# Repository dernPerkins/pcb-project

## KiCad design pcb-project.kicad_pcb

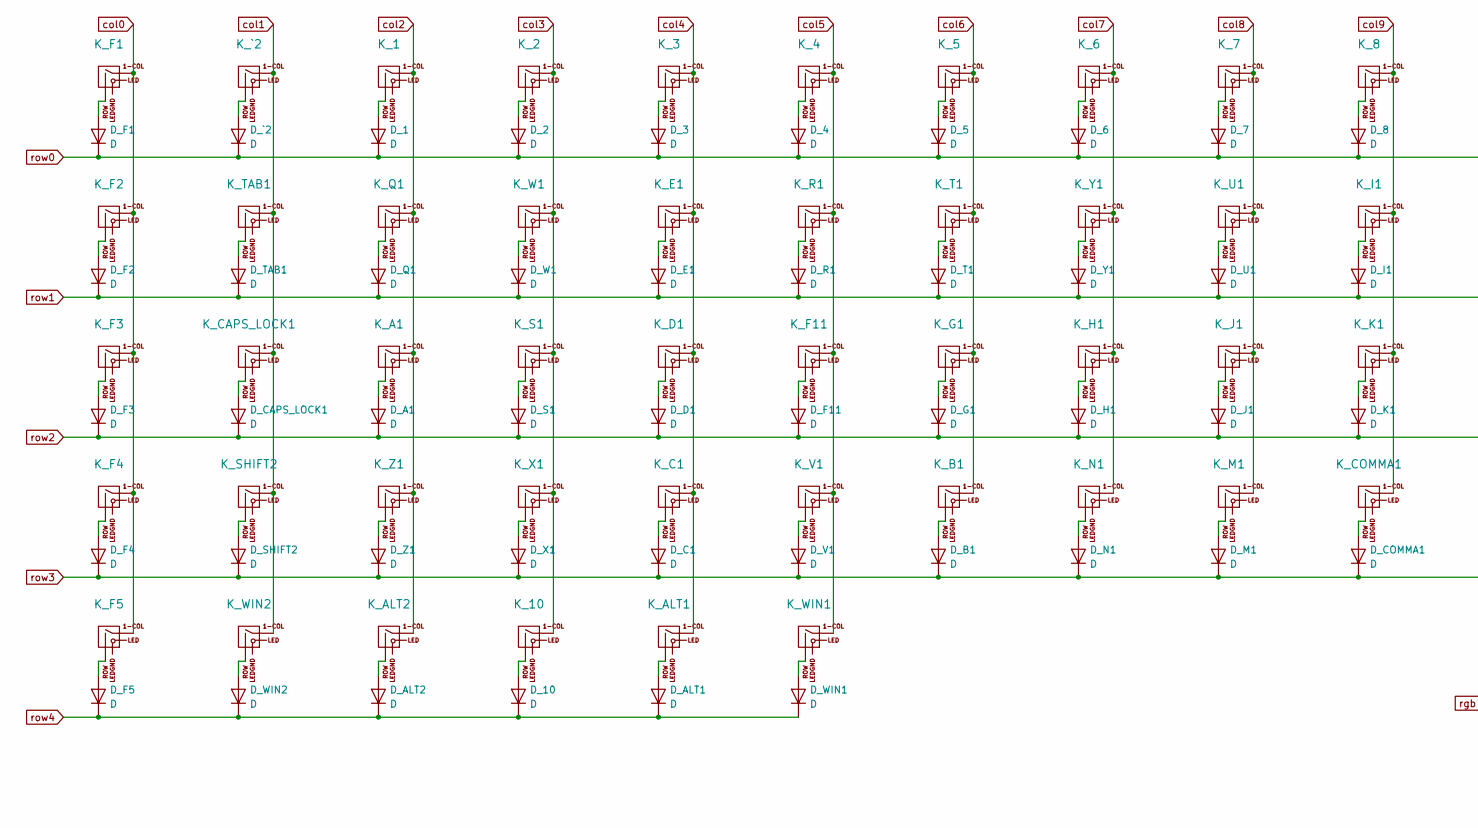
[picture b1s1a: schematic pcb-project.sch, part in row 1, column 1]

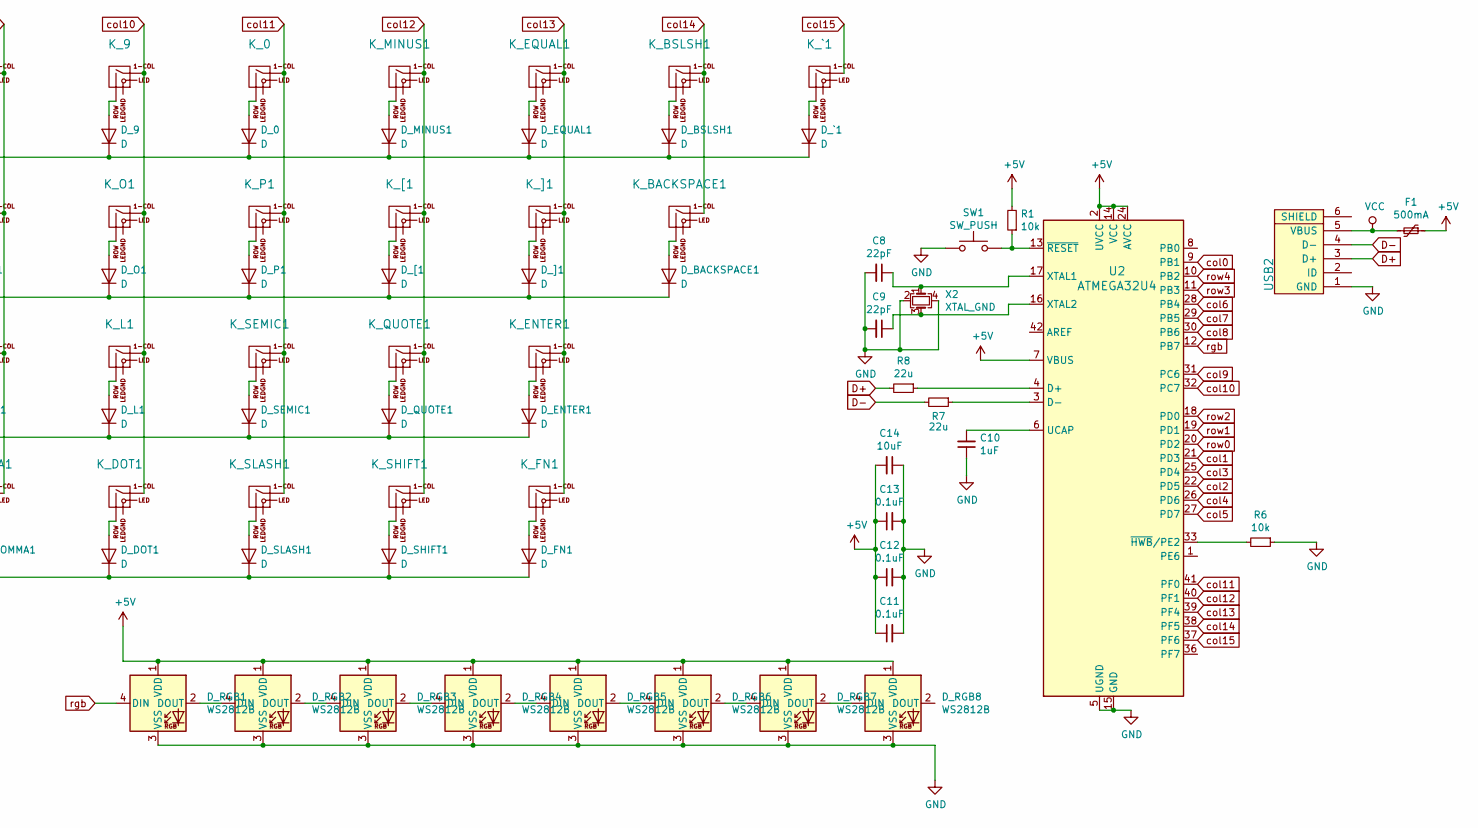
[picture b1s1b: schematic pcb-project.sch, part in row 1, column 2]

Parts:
C8, C9: 22pF; C_0805_2012Metric
C10: 1uF; C_0805_2012Metric
C11, C12, C13: 0.1uF; C_0805_2012Metric
C14: 10uF; C_0805_2012Metric
D_0, D_1, D_2, D_3, D_4, D_5, D_6, D_7, D_8, D_9, D_10: D; D_SOD-123-Pretty
D_A1: D; D_SOD-123-Pretty
D_ALT1, D_ALT2: D; D_SOD-123-Pretty
D_B1: D; D_SOD-123-Pretty
D_BACKSPACE1: D; D_SOD-123-Pretty
D_BSLSH1: D; D_SOD-123-Pretty
D_C1: D; D_SOD-123-Pretty
D_CAPS_LOCK1: D; D_SOD-123-Pretty
D_COMMA1: D; D_SOD-123-Pretty
D_D1: D; D_SOD-123-Pretty
D_DOT1: D; D_SOD-123-Pretty
D_E1: D; D_SOD-123-Pretty
D_ENTER1: D; D_SOD-123-Pretty
D_EQUAL1: D; D_SOD-123-Pretty
D_F1, D_F2, D_F3, D_F4, D_F5, D_F11: D; D_SOD-123-Pretty
D_FN1: D; D_SOD-123-Pretty
D_G1: D; D_SOD-123-Pretty
D_H1: D; D_SOD-123-Pretty
D_I1: D; D_SOD-123-Pretty
D_J1: D; D_SOD-123-Pretty
D_K1: D; D_SOD-123-Pretty
D_L1: D; D_SOD-123-Pretty
D_M1: D; D_SOD-123-Pretty
D_MINUS1: D; D_SOD-123-Pretty
D_N1: D; D_SOD-123-Pretty
D_O1: D; D_SOD-123-Pretty
D_P1: D; D_SOD-123-Pretty
D_Q1: D; D_SOD-123-Pretty
D_QUOTE1: D; D_SOD-123-Pretty
D_R1: D; D_SOD-123-Pretty
D_RGB1, D_RGB2, D_RGB3, D_RGB4, D_RGB5, D_RGB6, D_RGB7, D_RGB8: WS2812B; LED_WS2812B_PLCC4_5.0x5.0mm_P3.2mm
D_S1: D; D_SOD-123-Pretty
D_SEMIC1: D; D_SOD-123-Pretty
D_SHIFT1, D_SHIFT2: D; D_SOD-123-Pretty
D_SLASH1: D; D_SOD-123-Pretty
D_T1: D; D_SOD-123-Pretty
D_TAB1: D; D_SOD-123-Pretty
D_U1: D; D_SOD-123-Pretty
D_V1: D; D_SOD-123-Pretty
D_W1: D; D_SOD-123-Pretty
D_WIN1, D_WIN2: D; D_SOD-123-Pretty
D_X1: D; D_SOD-123-Pretty
D_Y1: D; D_SOD-123-Pretty
D_Z1: D; D_SOD-123-Pretty
D_[1: D; D_SOD-123-Pretty
D_]1: D; D_SOD-123-Pretty
D_`1, D_`2: D; D_SOD-123-Pretty
F1: 500mA; Fuse_1206_3216Metric
K_0, K_1, K_2, K_3, K_4, K_5, K_6, K_7, K_8, K_9: KEYSW; MX-1U-NoLED
K_10: KEYSW; MX-7U-NoLED
K_A1: KEYSW; MX-1U-NoLED
K_ALT1, K_ALT2: KEYSW; MX-1.5U-NoLED
K_B1: KEYSW; MX-1U-NoLED
K_BACKSPACE1: KEYSW; MX-1.5U-NoLED
K_BSLSH1: KEYSW; MX-1U-NoLED
K_C1: KEYSW; MX-1U-NoLED
K_CAPS_LOCK1: KEYSW; MX-1.75U-NoLED
K_COMMA1: KEYSW; MX-1U-NoLED
K_D1: KEYSW; MX-1U-NoLED
K_DOT1: KEYSW; MX-1U-NoLED
K_E1: KEYSW; MX-1U-NoLED
K_ENTER1: KEYSW; MX-2.25U-NoLED
K_EQUAL1: KEYSW; MX-1U-NoLED
K_F1, K_F2, K_F3, K_F4, K_F5, K_F11: KEYSW; MX-1U-NoLED
K_FN1: KEYSW; MX-1U-NoLED
K_G1: KEYSW; MX-1U-NoLED
K_H1: KEYSW; MX-1U-NoLED
K_I1: KEYSW; MX-1U-NoLED
K_J1: KEYSW; MX-1U-NoLED
K_K1: KEYSW; MX-1U-NoLED
K_L1: KEYSW; MX-1U-NoLED
K_M1: KEYSW; MX-1U-NoLED
K_MINUS1: KEYSW; MX-1U-NoLED
K_N1: KEYSW; MX-1U-NoLED
K_O1: KEYSW; MX-1U-NoLED
K_P1: KEYSW; MX-1U-NoLED
K_Q1: KEYSW; MX-1U-NoLED
K_QUOTE1: KEYSW; MX-1U-NoLED
K_R1: KEYSW; MX-1U-NoLED
K_S1: KEYSW; MX-1U-NoLED
K_SEMIC1: KEYSW; MX-1U-NoLED
K_SHIFT1: KEYSW; MX-1.75U-NoLED
K_SHIFT2: KEYSW; MX-2.25U-NoLED
K_SLASH1: KEYSW; MX-1U-NoLED
K_T1: KEYSW; MX-1U-NoLED
K_TAB1: KEYSW; MX-1.5U-NoLED
K_U1: KEYSW; MX-1U-NoLED
K_V1: KEYSW; MX-1U-NoLED
K_W1: KEYSW; MX-1U-NoLED
K_WIN1, K_WIN2: KEYSW; MX-1U-NoLED
K_X1: KEYSW; MX-1U-NoLED
K_Y1: KEYSW; MX-1U-NoLED
K_Z1: KEYSW; MX-1U-NoLED
K_[1: KEYSW; MX-1U-NoLED
K_]1: KEYSW; MX-1U-NoLED
K_`1, K_`2: KEYSW; MX-1U-NoLED
R1, R6: 10k; R_0805_2012Metric
R7, R8: 22u; R_0805_2012Metric
SW1: SW_PUSH; SKQG-1155865
U2: ATMEGA32U4; TQFP-44_10x10mm_P0.8mm
USB2: USB_mini_micro_B; Molex-0548190589
X2: XTAL_GND; Crystal_SMD_3225-4Pin_3.2x2.5mm

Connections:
+5V: C11.1, C12.1, C13.1, C14.2, D_RGB1.1 (VDD), D_RGB2.1 (VDD), D_RGB3.1 (VDD), D_RGB4.1 (VDD), D_RGB5.1 (VDD), D_RGB6.1 (VDD), D_RGB7.1 (VDD), D_RGB8.1 (VDD), F1.1, R1.2, U2.2 (UVCC), U2.7 (VBUS), U2.14 (VCC), U2.24 (AVCC), U2.34 (VCC), U2.44 (AVCC)
D+: R8.2, USB2.3 (D+)
D-: R7.2, USB2.4 (D-)
GND: C8.2, C9.2, C10.1, C11.2, C12.2, C13.2, C14.1, D_RGB1.3 (VSS), D_RGB2.3 (VSS), D_RGB3.3 (VSS), D_RGB4.3 (VSS), D_RGB5.3 (VSS), D_RGB6.3 (VSS), D_RGB7.3 (VSS), D_RGB8.3 (VSS), R6.1, SW1.1, U2.5 (UGND), U2.15 (GND), U2.23 (GND), U2.35 (GND), U2.43 (GND), USB2.1 (GND), X2.2, X2.4
unnamed: C8.1, U2.17 (XTAL1), X2.1
unnamed: C9.1, U2.16 (XTAL2), X2.3
unnamed: C10.2, U2.6 (UCAP)
unnamed: D_0.2 (A), K_0.2 (ROW)
unnamed: D_1.2 (A), K_1.2 (ROW)
unnamed: D_2.2 (A), K_2.2 (ROW)
unnamed: D_3.2 (A), K_3.2 (ROW)
unnamed: D_4.2 (A), K_4.2 (ROW)
unnamed: D_5.2 (A), K_5.2 (ROW)
unnamed: D_6.2 (A), K_6.2 (ROW)
unnamed: D_7.2 (A), K_7.2 (ROW)
unnamed: D_8.2 (A), K_8.2 (ROW)
unnamed: D_9.2 (A), K_9.2 (ROW)
unnamed: D_10.2 (A), K_10.2 (ROW)
unnamed: D_A1.2 (A), K_A1.2 (ROW)
unnamed: D_ALT1.2 (A), K_ALT1.2 (ROW)
unnamed: D_ALT2.2 (A), K_ALT2.2 (ROW)
unnamed: D_B1.2 (A), K_B1.2 (ROW)
unnamed: D_BACKSPACE1.2 (A), K_BACKSPACE1.2 (ROW)
unnamed: D_BSLSH1.2 (A), K_BSLSH1.2 (ROW)
unnamed: D_C1.2 (A), K_C1.2 (ROW)
unnamed: D_CAPS_LOCK1.2 (A), K_CAPS_LOCK1.2 (ROW)
unnamed: D_COMMA1.2 (A), K_COMMA1.2 (ROW)
unnamed: D_D1.2 (A), K_D1.2 (ROW)
unnamed: D_DOT1.2 (A), K_DOT1.2 (ROW)
unnamed: D_E1.2 (A), K_E1.2 (ROW)
unnamed: D_ENTER1.2 (A), K_ENTER1.2 (ROW)
unnamed: D_EQUAL1.2 (A), K_EQUAL1.2 (ROW)
unnamed: D_F1.2 (A), K_F1.2 (ROW)
unnamed: D_F2.2 (A), K_F2.2 (ROW)
unnamed: D_F3.2 (A), K_F3.2 (ROW)
unnamed: D_F4.2 (A), K_F4.2 (ROW)
unnamed: D_F5.2 (A), K_F5.2 (ROW)
unnamed: D_F11.2 (A), K_F11.2 (ROW)
unnamed: D_FN1.2 (A), K_FN1.2 (ROW)
unnamed: D_G1.2 (A), K_G1.2 (ROW)
unnamed: D_H1.2 (A), K_H1.2 (ROW)
unnamed: D_I1.2 (A), K_I1.2 (ROW)
unnamed: D_J1.2 (A), K_J1.2 (ROW)
unnamed: D_K1.2 (A), K_K1.2 (ROW)
unnamed: D_L1.2 (A), K_L1.2 (ROW)
unnamed: D_M1.2 (A), K_M1.2 (ROW)
unnamed: D_MINUS1.2 (A), K_MINUS1.2 (ROW)
unnamed: D_N1.2 (A), K_N1.2 (ROW)
unnamed: D_O1.2 (A), K_O1.2 (ROW)
unnamed: D_P1.2 (A), K_P1.2 (ROW)
unnamed: D_Q1.2 (A), K_Q1.2 (ROW)
unnamed: D_QUOTE1.2 (A), K_QUOTE1.2 (ROW)
unnamed: D_R1.2 (A), K_R1.2 (ROW)
unnamed: D_RGB1.2 (DOUT), D_RGB2.4 (DIN)
unnamed: D_RGB2.2 (DOUT), D_RGB3.4 (DIN)
unnamed: D_RGB3.2 (DOUT), D_RGB4.4 (DIN)
unnamed: D_RGB4.2 (DOUT), D_RGB5.4 (DIN)
unnamed: D_RGB5.2 (DOUT), D_RGB6.4 (DIN)
unnamed: D_RGB6.2 (DOUT), D_RGB7.4 (DIN)
unnamed: D_RGB7.2 (DOUT), D_RGB8.4 (DIN)
unnamed: D_S1.2 (A), K_S1.2 (ROW)
unnamed: D_SEMIC1.2 (A), K_SEMIC1.2 (ROW)
unnamed: D_SHIFT1.2 (A), K_SHIFT1.2 (ROW)
unnamed: D_SHIFT2.2 (A), K_SHIFT2.2 (ROW)
unnamed: D_SLASH1.2 (A), K_SLASH1.2 (ROW)
unnamed: D_T1.2 (A), K_T1.2 (ROW)
unnamed: D_TAB1.2 (A), K_TAB1.2 (ROW)
unnamed: D_U1.2 (A), K_U1.2 (ROW)
unnamed: D_V1.2 (A), K_V1.2 (ROW)
unnamed: D_W1.2 (A), K_W1.2 (ROW)
unnamed: D_WIN1.2 (A), K_WIN1.2 (ROW)
unnamed: D_WIN2.2 (A), K_WIN2.2 (ROW)
unnamed: D_X1.2 (A), K_X1.2 (ROW)
unnamed: D_Y1.2 (A), K_Y1.2 (ROW)
unnamed: D_Z1.2 (A), K_Z1.2 (ROW)
unnamed: D_[1.2 (A), K_[1.2 (ROW)
unnamed: D_]1.2 (A), K_]1.2 (ROW)
unnamed: D_`1.2 (A), K_`1.2 (ROW)
unnamed: D_`2.2 (A), K_`2.2 (ROW)
unnamed: R1.1, SW1.2, U2.13 (~RESET)
unnamed: R6.2, U2.33 (~HWB~/PE2)
unnamed: R7.1, U2.3 (D-)
unnamed: R8.1, U2.4 (D+)
VCC: F1.2, USB2.5 (VBUS)
col0: K_F1.1 (COL), K_F2.1 (COL), K_F3.1 (COL), K_F4.1 (COL), K_F5.1 (COL), U2.9 (PB1)
col1: K_CAPS_LOCK1.1 (COL), K_SHIFT2.1 (COL), K_TAB1.1 (COL), K_WIN2.1 (COL), K_`2.1 (COL), U2.21 (PD3)
col2: K_1.1 (COL), K_A1.1 (COL), K_ALT2.1 (COL), K_Q1.1 (COL), K_Z1.1 (COL), U2.22 (PD5)
col3: K_2.1 (COL), K_10.1 (COL), K_S1.1 (COL), K_W1.1 (COL), K_X1.1 (COL), U2.25 (PD4)
col4: K_3.1 (COL), K_ALT1.1 (COL), K_C1.1 (COL), K_D1.1 (COL), K_E1.1 (COL), U2.26 (PD6)
col5: K_4.1 (COL), K_F11.1 (COL), K_R1.1 (COL), K_V1.1 (COL), K_WIN1.1 (COL), U2.27 (PD7)
col6: K_5.1 (COL), K_B1.1 (COL), K_G1.1 (COL), K_T1.1 (COL), U2.28 (PB4)
col7: K_6.1 (COL), K_H1.1 (COL), K_N1.1 (COL), K_Y1.1 (COL), U2.29 (PB5)
col8: K_7.1 (COL), K_J1.1 (COL), K_M1.1 (COL), K_U1.1 (COL), U2.30 (PB6)
col9: K_8.1 (COL), K_COMMA1.1 (COL), K_I1.1 (COL), K_K1.1 (COL), U2.31 (PC6)
col10: K_9.1 (COL), K_DOT1.1 (COL), K_L1.1 (COL), K_O1.1 (COL), U2.32 (PC7)
col11: K_0.1 (COL), K_P1.1 (COL), K_SEMIC1.1 (COL), K_SLASH1.1 (COL), U2.41 (PF0)
col12: K_MINUS1.1 (COL), K_QUOTE1.1 (COL), K_SHIFT1.1 (COL), K_[1.1 (COL), U2.40 (PF1)
col13: K_ENTER1.1 (COL), K_EQUAL1.1 (COL), K_FN1.1 (COL), K_]1.1 (COL), U2.39 (PF4)
col14: K_BACKSPACE1.1 (COL), K_BSLSH1.1 (COL), U2.38 (PF5)
col15: K_`1.1 (COL), U2.37 (PF6)
rgb: D_RGB1.4 (DIN), U2.12 (PB7)
row0: D_0.1 (K), D_1.1 (K), D_2.1 (K), D_3.1 (K), D_4.1 (K), D_5.1 (K), D_6.1 (K), D_7.1 (K), D_8.1 (K), D_9.1 (K), D_BSLSH1.1 (K), D_EQUAL1.1 (K), D_F1.1 (K), D_MINUS1.1 (K), D_`1.1 (K), D_`2.1 (K), U2.20 (PD2)
row1: D_BACKSPACE1.1 (K), D_E1.1 (K), D_F2.1 (K), D_I1.1 (K), D_O1.1 (K), D_P1.1 (K), D_Q1.1 (K), D_R1.1 (K), D_T1.1 (K), D_TAB1.1 (K), D_U1.1 (K), D_W1.1 (K), D_Y1.1 (K), D_[1.1 (K), D_]1.1 (K), U2.19 (PD1)
row2: D_A1.1 (K), D_CAPS_LOCK1.1 (K), D_D1.1 (K), D_ENTER1.1 (K), D_F3.1 (K), D_F11.1 (K), D_G1.1 (K), D_H1.1 (K), D_J1.1 (K), D_K1.1 (K), D_L1.1 (K), D_QUOTE1.1 (K), D_S1.1 (K), D_SEMIC1.1 (K), U2.18 (PD0)
row3: D_B1.1 (K), D_C1.1 (K), D_COMMA1.1 (K), D_DOT1.1 (K), D_F4.1 (K), D_FN1.1 (K), D_M1.1 (K), D_N1.1 (K), D_SHIFT1.1 (K), D_SHIFT2.1 (K), D_SLASH1.1 (K), D_V1.1 (K), D_X1.1 (K), D_Z1.1 (K), U2.11 (PB3)
row4: D_10.1 (K), D_ALT1.1 (K), D_ALT2.1 (K), D_F5.1 (K), D_WIN1.1 (K), D_WIN2.1 (K), U2.10 (PB2)

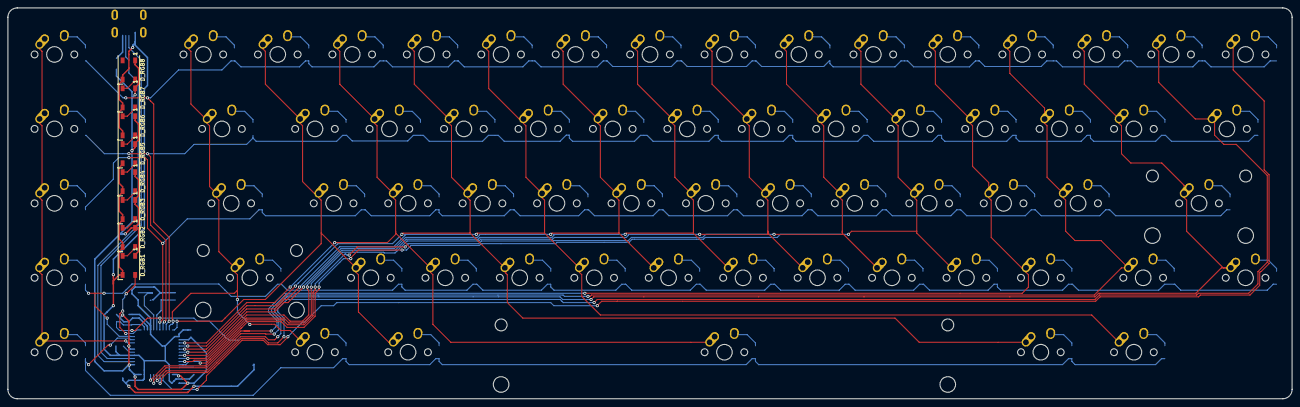
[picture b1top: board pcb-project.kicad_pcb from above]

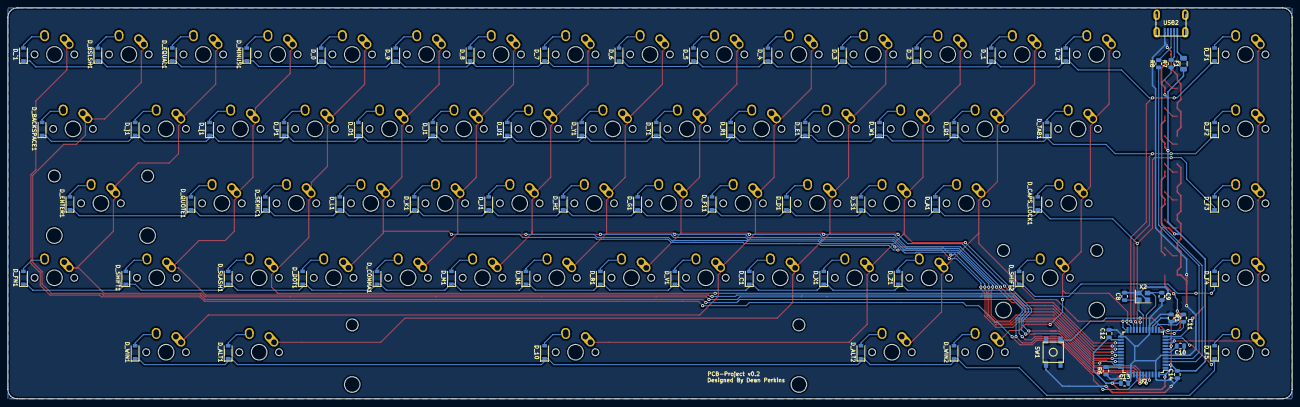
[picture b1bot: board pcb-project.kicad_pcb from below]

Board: 2 copper layers, 328.6 x 100.0 mm, 154 parts (81 on the bottom side), 106 nets.

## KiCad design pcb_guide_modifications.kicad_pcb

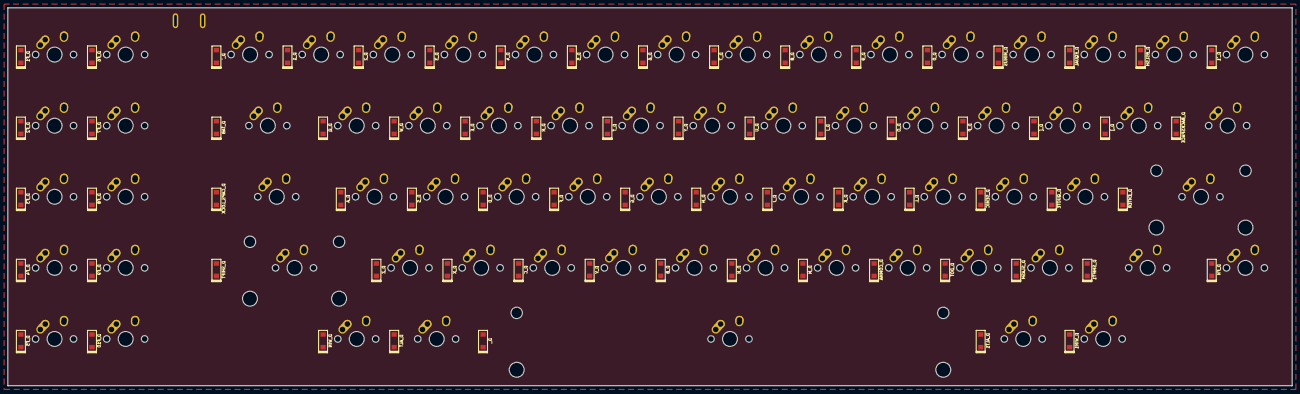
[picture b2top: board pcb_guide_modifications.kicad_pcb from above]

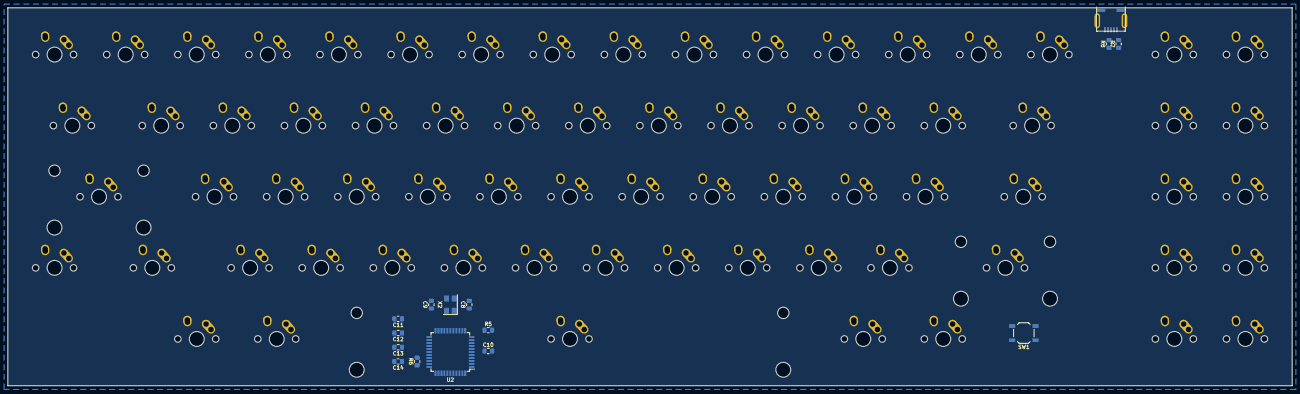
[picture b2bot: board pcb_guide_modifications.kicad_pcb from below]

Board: 2 copper layers, 344.1 x 101.2 mm, 155 parts (15 on the bottom side), 97 nets, no tracks yet.

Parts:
C8, C9, C10, C11, C12, C13, C14: 22pF; C_0805_2012Metric_Pad1.15x1.40mm_HandSolder
D_, D_0, D_1, D_2, D_3, D_4, D_5, D_6, D_7, D_8, D_9: D; D_SOD123
D_A: D; D_SOD123
D_ALT, D_ALT1: D; D_SOD123
D_B: D; D_SOD123
D_BACKSPACE: D; D_SOD123
D_BSLSH: D; D_SOD123
D_C: D; D_SOD123
D_CAPS_LOCK: D; D_SOD123
D_COMMA: D; D_SOD123
D_D: D; D_SOD123
D_DOT: D; D_SOD123
D_E: D; D_SOD123
D_ENTER: D; D_SOD123
D_EQUAL: D; D_SOD123
D_F, D_F1, D_F2, D_F3, D_F4, D_F5, D_F6, D_F7, D_F8, D_F9, D_F10: D; D_SOD123
D_FN: D; D_SOD123
D_G: D; D_SOD123
D_H: D; D_SOD123
D_I: D; D_SOD123
D_J: D; D_SOD123
D_K: D; D_SOD123
D_L: D; D_SOD123
D_M: D; D_SOD123
D_MINUS: D; D_SOD123
D_N: D; D_SOD123
D_O: D; D_SOD123
D_P: D; D_SOD123
D_Q: D; D_SOD123
D_QUOTE: D; D_SOD123
D_R: D; D_SOD123
D_S: D; D_SOD123
D_SEMIC: D; D_SOD123
D_SHIFT, D_SHIFT1: D; D_SOD123
D_SLASH: D; D_SOD123
D_T: D; D_SOD123
D_TAB: D; D_SOD123
D_U: D; D_SOD123
D_V: D; D_SOD123
D_W: D; D_SOD123
D_WIN, D_WIN1: D; D_SOD123
D_X: D; D_SOD123
D_Y: D; D_SOD123
D_Z: D; D_SOD123
D_[: D; D_SOD123
D_]: D; D_SOD123
D_`, D_`1: D; D_SOD123
K_: KEYSW; MX-7U-NoLED
K_0, K_1, K_2, K_3, K_4, K_5, K_6, K_7, K_8, K_9: KEYSW; MX-1U-NoLED
K_A: KEYSW; MX-1U-NoLED
K_ALT, K_ALT1: KEYSW; MX-1.25U-NoLED
K_B: KEYSW; MX-1U-NoLED
K_BACKSPACE: KEYSW; MX-1.5U-NoLED
K_BSLSH: KEYSW; MX-1U-NoLED
K_C: KEYSW; MX-1U-NoLED
K_CAPS_LOCK: KEYSW; MX-1.75U-NoLED
K_COMMA: KEYSW; MX-1U-NoLED
K_D: KEYSW; MX-1U-NoLED
K_DOT: KEYSW; MX-1U-NoLED
K_E: KEYSW; MX-1U-NoLED
K_ENTER: KEYSW; MX-2.25U-NoLED
K_EQUAL: KEYSW; MX-1U-NoLED
K_F, K_F1, K_F2, K_F3, K_F4, K_F5, K_F6, K_F7, K_F8, K_F9, K_F10: KEYSW; MX-1U-NoLED
K_FN: KEYSW; MX-1U-NoLED
K_G: KEYSW; MX-1U-NoLED
K_H: KEYSW; MX-1U-NoLED
K_I: KEYSW; MX-1U-NoLED
K_J: KEYSW; MX-1U-NoLED
K_K: KEYSW; MX-1U-NoLED
K_L: KEYSW; MX-1U-NoLED
K_M: KEYSW; MX-1U-NoLED
K_MINUS: KEYSW; MX-1U-NoLED
K_N: KEYSW; MX-1U-NoLED
K_O: KEYSW; MX-1U-NoLED
K_P: KEYSW; MX-1U-NoLED
K_Q: KEYSW; MX-1U-NoLED
K_QUOTE: KEYSW; MX-1U-NoLED
K_R: KEYSW; MX-1U-NoLED
K_S: KEYSW; MX-1U-NoLED
K_SEMIC: KEYSW; MX-1U-NoLED
K_SHIFT: KEYSW; MX-2.25U-NoLED
K_SHIFT1: KEYSW; MX-1.75U-NoLED
K_SLASH: KEYSW; MX-1U-NoLED
K_T: KEYSW; MX-1U-NoLED
K_TAB: KEYSW; MX-1.5U-NoLED
K_U: KEYSW; MX-1U-NoLED
K_V: KEYSW; MX-1U-NoLED
K_W: KEYSW; MX-1U-NoLED
K_WIN, K_WIN1: KEYSW; MX-1U-NoLED
K_X: KEYSW; MX-1U-NoLED
K_Y: KEYSW; MX-1U-NoLED
K_Z: KEYSW; MX-1U-NoLED
K_[: KEYSW; MX-1U-NoLED
K_]: KEYSW; MX-1U-NoLED
K_`, K_`1: KEYSW; MX-1U-NoLED
R5, R6: 10k; R_0805_2012Metric_Pad1.15x1.40mm_HandSolder
R7, R8: 22u; R_0805_2012Metric_Pad1.15x1.40mm_HandSolder
SW1: SW_PUSH; SW_SPST_TL3342
U2: ATMEGA32U4; TQFP-44_10x10mm_P0.8mm
USB2: USB_mini_micro_B; USB_miniB_hirose_5S8
X2: XTAL_GND; Crystal_SMD_5032-4Pin_5.0x3.2mm

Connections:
/col0: D_F1.1, D_F2.1, D_F3.1, D_F4.1, D_F5.1, U2.32
/col1: D_F6.1, D_F7.1, D_F8.1, D_F9.1, D_F10.1, U2.31
/col2: D_CAPS_LOCK.1, D_SHIFT.1, D_TAB.1, D_WIN.1, D_`.1, U2.12
/col3: D_1.1, D_A.1, D_ALT.1, D_Q.1, D_Z.1, U2.30
/col4: D_.1, D_2.1, D_S.1, D_W.1, D_X.1, U2.29
/col5: D_3.1, D_ALT1.1, D_C.1, D_D.1, D_E.1, U2.28
/col6: D_4.1, D_F.1, D_R.1, D_V.1, D_WIN1.1, U2.11
/col7: D_5.1, D_B.1, D_G.1, D_T.1, U2.10
/col8: D_6.1, D_H.1, D_N.1, D_Y.1, U2.9
/col9: D_7.1, D_J.1, D_M.1, D_U.1, U2.8
/col10: D_8.1, D_COMMA.1, D_I.1, D_K.1, U2.37
/col11: D_9.1, D_DOT.1, D_L.1, D_O.1, U2.38
/col12: D_0.1, D_P.1, D_SEMIC.1, D_SLASH.1, U2.39
/col13: D_MINUS.1, D_QUOTE.1, D_SHIFT1.1, D_[.1, U2.40
/col14: D_ENTER.1, D_EQUAL.1, D_FN.1, D_].1, U2.41
/col15: D_BACKSPACE.1, D_BSLSH.1
GND: C8.2, C9.2, C10.2, C11.2, C12.2, C13.2, C14.2, R6.2, SW1.1, U2.5, U2.15, U2.23, USB2.5, USB2.6, X2.3
unnamed: C8.1, U2.16
unnamed: C9.1, U2.17
unnamed: C10.1, U2.6
unnamed: D_0.2, K_0.2
unnamed: D_1.2, K_1.2
unnamed: D_2.2, K_2.2
unnamed: D_3.2, K_3.2
unnamed: D_4.2, K_4.2
unnamed: D_5.2, K_5.2
unnamed: D_6.2, K_6.2
unnamed: D_7.2, K_7.2
unnamed: D_8.2, K_8.2
unnamed: D_9.2, K_9.2
unnamed: D_.2, K_.2
unnamed: D_A.2, K_A.2
unnamed: D_ALT1.2, K_ALT1.2
unnamed: D_ALT.2, K_ALT.2
unnamed: D_B.2, K_B.2
unnamed: D_BACKSPACE.2, K_BACKSPACE.2
unnamed: D_BSLSH.2, K_BSLSH.2
unnamed: D_C.2, K_C.2
unnamed: D_CAPS_LOCK.2, K_CAPS_LOCK.2
unnamed: D_COMMA.2, K_COMMA.2
unnamed: D_D.2, K_D.2
unnamed: D_DOT.2, K_DOT.2
unnamed: D_E.2, K_E.2
unnamed: D_ENTER.2, K_ENTER.2
unnamed: D_EQUAL.2, K_EQUAL.2
unnamed: D_F1.2, K_F1.2
unnamed: D_F2.2, K_F2.2
unnamed: D_F3.2, K_F3.2
unnamed: D_F4.2, K_F4.2
unnamed: D_F5.2, K_F5.2
unnamed: D_F6.2, K_F6.2
unnamed: D_F7.2, K_F7.2
unnamed: D_F8.2, K_F8.2
unnamed: D_F9.2, K_F9.2
unnamed: D_F10.2, K_F10.2
unnamed: D_F.2, K_F.2
unnamed: D_FN.2, K_FN.2
unnamed: D_G.2, K_G.2
unnamed: D_H.2, K_H.2
unnamed: D_I.2, K_I.2
unnamed: D_J.2, K_J.2
unnamed: D_K.2, K_K.2
unnamed: D_L.2, K_L.2
unnamed: D_M.2, K_M.2
unnamed: D_MINUS.2, K_MINUS.2
unnamed: D_N.2, K_N.2
unnamed: D_O.2, K_O.2
unnamed: D_P.2, K_P.2
unnamed: D_Q.2, K_Q.2
unnamed: D_QUOTE.2, K_QUOTE.2
unnamed: D_R.2, K_R.2
unnamed: D_S.2, K_S.2
unnamed: D_SEMIC.2, K_SEMIC.2
unnamed: D_SHIFT1.2, K_SHIFT1.2
unnamed: D_SHIFT.2, K_SHIFT.2
unnamed: D_SLASH.2, K_SLASH.2
unnamed: D_T.2, K_T.2
unnamed: D_TAB.2, K_TAB.2
unnamed: D_U.2, K_U.2
unnamed: D_V.2, K_V.2
unnamed: D_W.2, K_W.2
unnamed: D_WIN1.2, K_WIN1.2
unnamed: D_WIN.2, K_WIN.2
unnamed: D_X.2, K_X.2
unnamed: D_Y.2, K_Y.2
unnamed: D_Z.2, K_Z.2
unnamed: D_[.2, K_[.2
unnamed: D_].2, K_].2
unnamed: D_`1.2, K_`1.2
unnamed: D_`.2, K_`.2
unnamed: R5.1, SW1.2, U2.13
unnamed: R6.1, U2.33
unnamed: R7.1, U2.3
unnamed: R8.1, U2.4
unnamed: R7.2, USB2.2
unnamed: R8.2, USB2.3
VCC: C11.1, C12.1, C13.1, C14.1, R5.2, U2.2, U2.14, U2.24, USB2.1

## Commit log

2019-03-22 Initial Check In
    These are the files that I've been working with currently for this project. Everything as of right now has been done with the MrKeebs PCB Generator and some moving of components in KiCad.
2019-03-22 Completed Schematic
    Followed the guide here https://kbwiki.ai03.me/books/pcb-design/chapter/pcb-designer-guide and added to the auto generated PCB all the proper stuff that was needed.
2019-03-22 Schematic with Footprints and Netlist
    This is a pre check in before I attempt to import the new net list and update/add/remove components based on the schematic.
2019-03-22 KiCad Netlist Import Keeps Failing
    Here is the net and pcb ready to be imported yet it keeps saying that the library footprints can't be found when I'm looking right at them. Going to need to take a crack at this later.
2019-03-25 New Handmade PCB and Schematic
    Basically swapped the whole thing with a schematic that essentially is the same as before, but with a fix to the footprints that were all broken. Created a pcb by hand that has no errors unlike the a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
2019-03-25 Added Traces
    No idea if they're entirely correct, hopefully can check it all out for myself and maybe have someone on Geekhack review it.
2019-03-26 Missing Matrix Connections
    The schematic and net list have been updated but this is prior to the pcb recieving the updated net list.
2019-03-26 Traces For Matrix
    All of the traces have been connected to the MCU pins.
2019-03-26 "Completed" PCB and Bongocat
    The PCB is basically done. Just wanted to add a decorative bongocat for a logo and then get the files that are actually used for production ready to go.
2019-03-28 Added some text to the PCB, added Gerber Files
2019-03-28 Changed Crystal on PCB to Spec. Recreated Gerber Files.
2019-03-28 Changed the Crystal to a different footprint
2019-04-04 Added Sandwich Case Files
2019-04-04 Updated the PCB with the uniform bottom row
2019-04-10 Latest Version of the PCB
    Had to modify the bottom row to use the proper 7u Spacebar and 1.5u Alts. Same as many uniform HHKB layout boards.
2019-05-02 Teensy Version of the PCB Project
2019-05-15 Schematic Update For RGB
2019-05-15 RGB Tracing Completed
    Ready for production files to be created and sent off to JLCPCB.
2019-05-17 Production Changes For RGB Addition
    Just followed the steps of getting the files for production and organizing the ordering sheet.
2019-06-08 Removed Unnecessary Resistor on RGB Data Trace
